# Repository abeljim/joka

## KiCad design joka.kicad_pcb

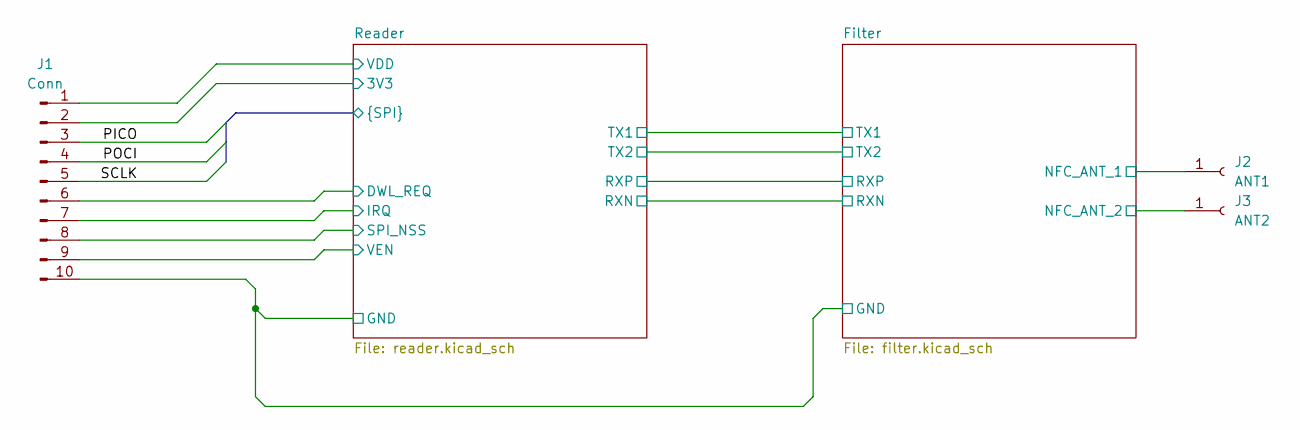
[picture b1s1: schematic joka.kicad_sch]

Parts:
J1: Conn; PinSocket_2x05_P2.54mm_Vertical
J2: ANT1; PinSocket_1x01_P2.54mm_Vertical
J3: ANT2; PinSocket_1x01_P2.54mm_Vertical

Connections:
/Filter/GND: J1.10; also elsewhere on the board
/Filter/NFC_ANT_1: J2.1; also elsewhere on the board
/Filter/NFC_ANT_2: J3.1; also elsewhere on the board
/Reader/3V3: J1.2; also elsewhere on the board
/Reader/DWL_REQ: J1.6; also elsewhere on the board
/Reader/IRQ: J1.7; also elsewhere on the board
/Reader/PICO: J1.3; also elsewhere on the board
/Reader/POCI: J1.4; also elsewhere on the board
/Reader/SCLK: J1.5; also elsewhere on the board
/Reader/SPI_NSS: J1.8; also elsewhere on the board
/Reader/VDD: J1.1; also elsewhere on the board
/Reader/VEN: J1.9; also elsewhere on the board

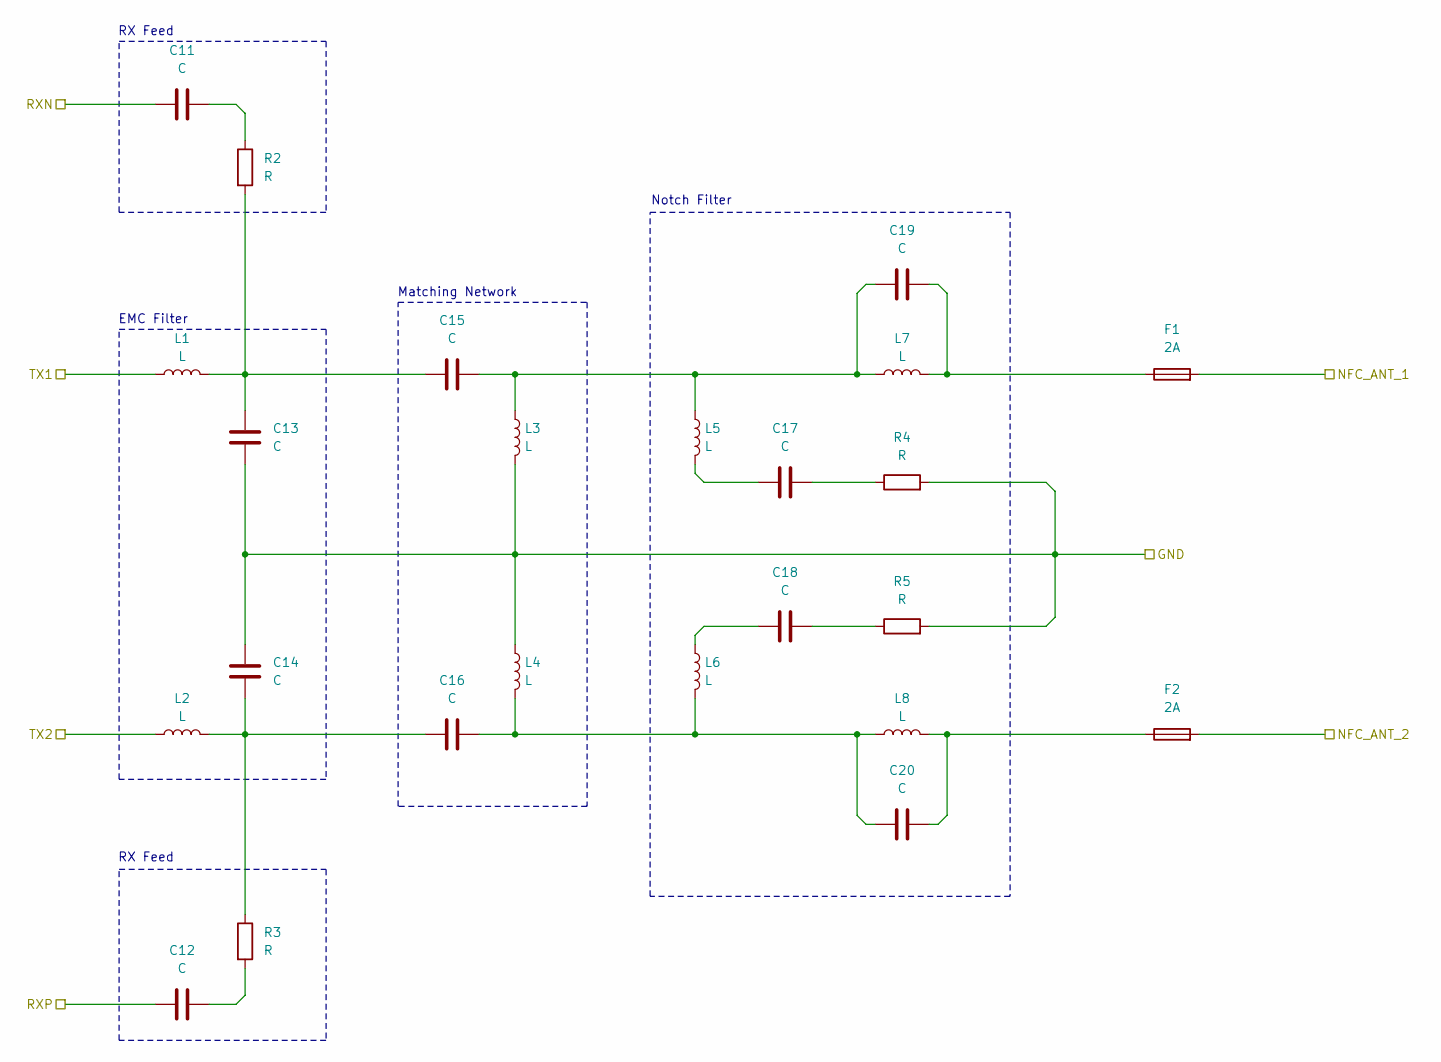
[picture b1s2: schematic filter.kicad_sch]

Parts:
C11, C12, C13, C14, C15, C16, C17, C18, C19, C20: C; C_0805_2012Metric
F1, F2: 2A; Fuse_0805_2012Metric
L1, L2, L3, L4, L5, L6, L7, L8: L; L_0805_2012Metric
R2, R3, R4, R5: R; R_0805_2012Metric

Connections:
/Filter/GND: C13.2, C14.1, L3.2, L4.1, R4.2, R5.2; also elsewhere on the board
/Filter/NFC_ANT_1: F1.2; also elsewhere on the board
/Filter/NFC_ANT_2: F2.2; also elsewhere on the board
/Filter/RXN: C11.1; also elsewhere on the board
/Filter/RXP: C12.1; also elsewhere on the board
/Filter/TX1: L1.1; also elsewhere on the board
/Filter/TX2: L2.1; also elsewhere on the board
unnamed: C11.2, R2.1
unnamed: C12.2, R3.2
unnamed: C13.1, C15.1, L1.2, R2.2
unnamed: C14.2, C16.1, L2.2, R3.1
unnamed: C15.2, C19.1, L3.1, L5.1, L7.1
unnamed: C16.2, C20.1, L4.2, L6.2, L8.1
unnamed: C17.1, L5.2
unnamed: C17.2, R4.1
unnamed: C18.1, L6.1
unnamed: C18.2, R5.1
unnamed: C19.2, F1.1, L7.2
unnamed: C20.2, F2.1, L8.2

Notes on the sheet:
Matching Network
RX Feed
EMC Filter
Notch Filter

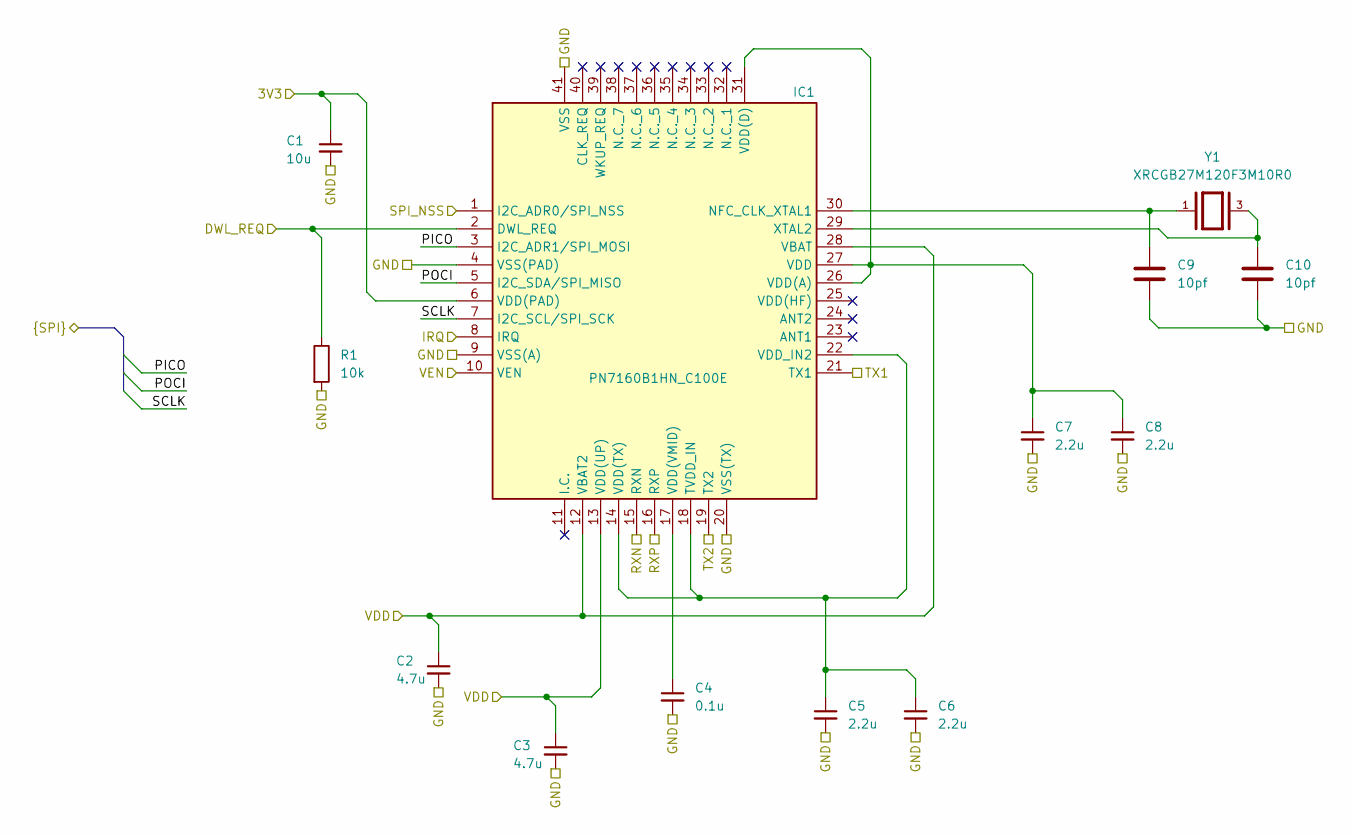
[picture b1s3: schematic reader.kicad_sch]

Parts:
C1: 10u; C_0805_2012Metric
C2, C3: 4.7u; C_0805_2012Metric
C4: 0.1u; C_0805_2012Metric
C5, C6, C7, C8: 2.2u; C_0805_2012Metric
C9, C10: 10pf; C_0805_2012Metric
IC1: PN7160B1HN_C100E; PN7160B1HNC100E; Manufacturer_Part_Number PN7160B1HN/C100E; Mouser Part Number 771-PN7160B1HN/C100E
R1: 10k; R_0805_2012Metric
Y1: XRCGB27M120F3M10R0

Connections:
/Filter/GND: C1.2, C2.2, C3.2, C4.2, C5.2, C6.2, C7.2, C8.2, C9.2, C10.2, IC1.4 (VSS(PAD)), IC1.9 (VSS(A)), IC1.20 (VSS(TX)), IC1.41 (VSS), R1.2; also elsewhere on the board
/Filter/RXN: IC1.15 (RXN); also elsewhere on the board
/Filter/RXP: IC1.16 (RXP); also elsewhere on the board
/Filter/TX1: IC1.21 (TX1); also elsewhere on the board
/Filter/TX2: IC1.19 (TX2); also elsewhere on the board
/Reader/3V3: C1.1, IC1.6 (VDD(PAD)); also elsewhere on the board
/Reader/DWL_REQ: IC1.2 (DWL_REQ), R1.1; also elsewhere on the board
/Reader/IRQ: IC1.8 (IRQ); also elsewhere on the board
/Reader/PICO: IC1.3 (I2C_ADR1/SPI_MOSI); also elsewhere on the board
/Reader/POCI: IC1.5 (I2C_SDA/SPI_MISO); also elsewhere on the board
/Reader/SCLK: IC1.7 (I2C_SCL/SPI_SCK); also elsewhere on the board
/Reader/SPI_NSS: IC1.1 (I2C_ADR0/SPI_NSS); also elsewhere on the board
/Reader/VDD: C2.1, C3.1, IC1.12 (VBAT2), IC1.13 (VDD(UP)), IC1.28 (VBAT); also elsewhere on the board
/Reader/VEN: IC1.10 (VEN); also elsewhere on the board
unnamed: C9.1, IC1.30 (NFC_CLK_XTAL1), Y1.1
unnamed: C5.1, C6.1, IC1.14 (VDD(TX)), IC1.18 (TVDD_IN), IC1.22 (VDD_IN2)
unnamed: C7.1, C8.1, IC1.26 (VDD(A)), IC1.27 (VDD), IC1.31 (VDD(D))
unnamed: C4.1, IC1.17 (VDD(VMID))
unnamed: C10.1, IC1.29 (XTAL2), Y1.3

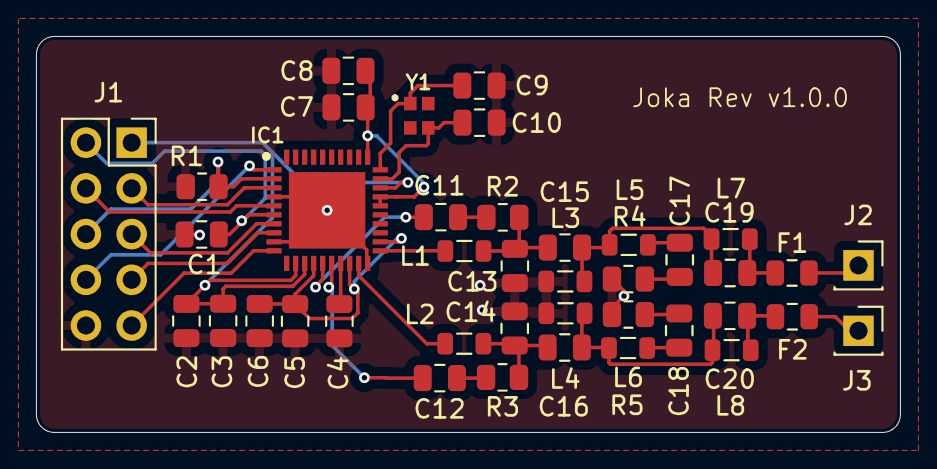
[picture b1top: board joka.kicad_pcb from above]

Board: 2 copper layers, 48.0 x 22.0 mm, 40 parts (0 on the bottom side), 33 nets.

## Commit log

2025-03-01 Configure Git LFS for STEP files
2025-03-01 added step file for main ic
2025-03-02 schematic is done
2025-03-02 added cicd
2025-03-03 intial version of pcb
